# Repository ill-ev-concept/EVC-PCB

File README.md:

# EVC-PCB

*By: Himesh Nasaka*

Welcome to EV Concept's PCB Repo!

This is where all of our projects are stored. 

* Boards: Contains design files of all current boards being worked on
* Libs: Contains a wide selection of schematics, footprints, and models of components that are being used

# Getting Started

Start by having Git and KiCAD 10 downloaded. If you are using a older version of KiCAD, we recommend updating to the newest version. We also recommend installing Github Desktop in order to make the usage a bit cleaner.

Clone this repo. This can be either done through terminal or Github Desktop. Click the green dropdown labeled "<> Code" and select your preference of how to clone the repo. If using terminal, run the command below

```git clone [INSERT]```

If using Desktop, you can click the dropdown menu next to current repository, then "add", and finally "clone" where we can input the repo's url. 

# Setting Paths

After cloning, open KiCAD and find the "Preferences" dropdown and select "Configure Paths".
We are going to be adding three new paths. Create three new variables, ```EVC_SYMBOL_DIR```, ```EVC_FOOTPRINT_DIR```, and ```EVC_3DMODEL_DIR```. Link these to the location of the ```symbols```, ```footprints```, and ```3d_models``` folders contained with ```libs``` folder.

When designing, we will need KiCAD to know to look at a given library. We can do this by going to "Preferences" and finding either "Manage Symbol Libraries" or "Manage Footprint Libraries". Opening either brings up a window where we can select "Project Specific Libraries" where we can add paths. Click the folder icon and add the wanted library. If you set the path up correctly, the library path will contain  ```${EVC_SYMBOL_DIR}```, ```${EVC_FOOTPRINT_DIR}```, or ```${EVC_3DMODEL_DIR}```. 

# Contributing 

In order to begin designing, create a branch for your given board. This can be done through either the "current branch" dropdown in Desktop or using the command ```git checkout -b [branch name]```. You can swap branches using the same dropdown or either ```git checkout [branch name]```. 

This will be the branch where you will be doing your design work. Create a new KiCAD project and save the location into the boards folder of this repo. Everything onward will be traditional git. Use ```git add``` or check off the needed boxes on Desktop to add files for commit. ```git commit -m "[MESSAGE HERE]"``` will commit your changes. Make sure to write a meaningful commit message in order for good documentation. An example is shown below.

```git commit -m "Finished designing LDO and CANBus connectors, need to add MCU pinout and decoupling caps"```

Input both your contributions and the next required steps in order to give reminders to both yourself and your teammates. 

Once a board is finished or you want it reviewed, it must be submitted via a pull request. This can be done using ```git push -u origin [branch name]``` or by clicking the branch dropdown in Desktop and selecting the "create pull request" option.

This will open up a Github tab on your browser where you can edit your pull request. Give it a good title and description so the design choices are clear and understandable. A title will also help the leads parse what you guys want done. 

You'll see the image above if you use a command line prompt and go to the repo.

After the PR is submitted, we will decide on whether the board can be pushed to main or not. If it is not pushed, we will submit comments on what needs to be reviewed and edited. You can view open PRs and their comments in Github.

Apart from designing in KiCAD, it is important to be updating the libs folder when any new schematic, footprint, or model is added. First make sure the IC you want to add isn't currently within our library. Add the path to the specific library which is detailed more above. If the IC is not located in it's library, open Symbol/Footprint editor and select the library you want to add to. I recommended clicking the "View" dropdown, selecting the "Panels" option and adding the "Library Tree" option in order to easily see the connected libraries. 

From this, import the downloaded model and save the file. From there, push the updated library files and create a pull request. The leads will then check your work and merge it into main so everyone can use the IC.

When making pull requests for ICs, make sure to push them individually rather than with changes to other files. This will make it more clear for reviewers to understand that library files are being edited in addition to making sure that the change will be pushed to main. If you push with changes to your board and the pull request is not granted, people will not have access to the IC you have imported. 

Because the libs folder will be constantly updated, its also important to keep your branch up to date with new changes. We can layer on changes from main into our branch using a few different methods but the main one we will be using is merge. Run the command ```git fetch origin``` and then ```git merge origin``` in order to update changes. In Desktop, you can select "Update from main" from the "Branch" dropdown. 

This should not change any local files that is stored and will update the libs folder to have the newest selection of ICs. I recommend doing this every time you work on your boards. It will also make sure a merge conflict won't be created, in which the same file from two different pull requests is edited, causing a lot of hassle for the writers of this repo. 

A general outline of what the workflow may look like is shown below:

```git checkout [branch name]``` -> Run this to swap to the branch you want to work on

```git fetch origin``` -> Run this to pull updates from main. Important for having updated libs

```git merge origin/main``` -> Merges the changes from the above command

```git add [file name]``` -> Add files for commit. When updating library files, make sure to add them in individual PRs

```git commit -m "[message here]"``` -> Commits your changes to be pushed into your branch

```git push -u origin [branch name]``` -> Run this command the first time you make the branch. It will link your branch to Github. 

```git push``` -> Pushes your changes. After, you can go to Github and create a pull request for the changes to be pushed into main. **Don't create a PR for every change you do.** Only create pull requests **IF** you are editing the libs folder **OR** you are submitting for board revision **OR** it is the final revision of the board.

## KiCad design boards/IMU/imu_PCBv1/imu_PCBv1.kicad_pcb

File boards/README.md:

# Boards!

This is the location where you will be pushing your KiCAD files to. 
Each file should be it's own project. You should only be pushing 5 different files
- kicad_pro
- kicad_sch
- kicad_pcb
- fp-lib-table
- sym-lib-table

*Nothing else should be pushed*

I'll be adding more details later on

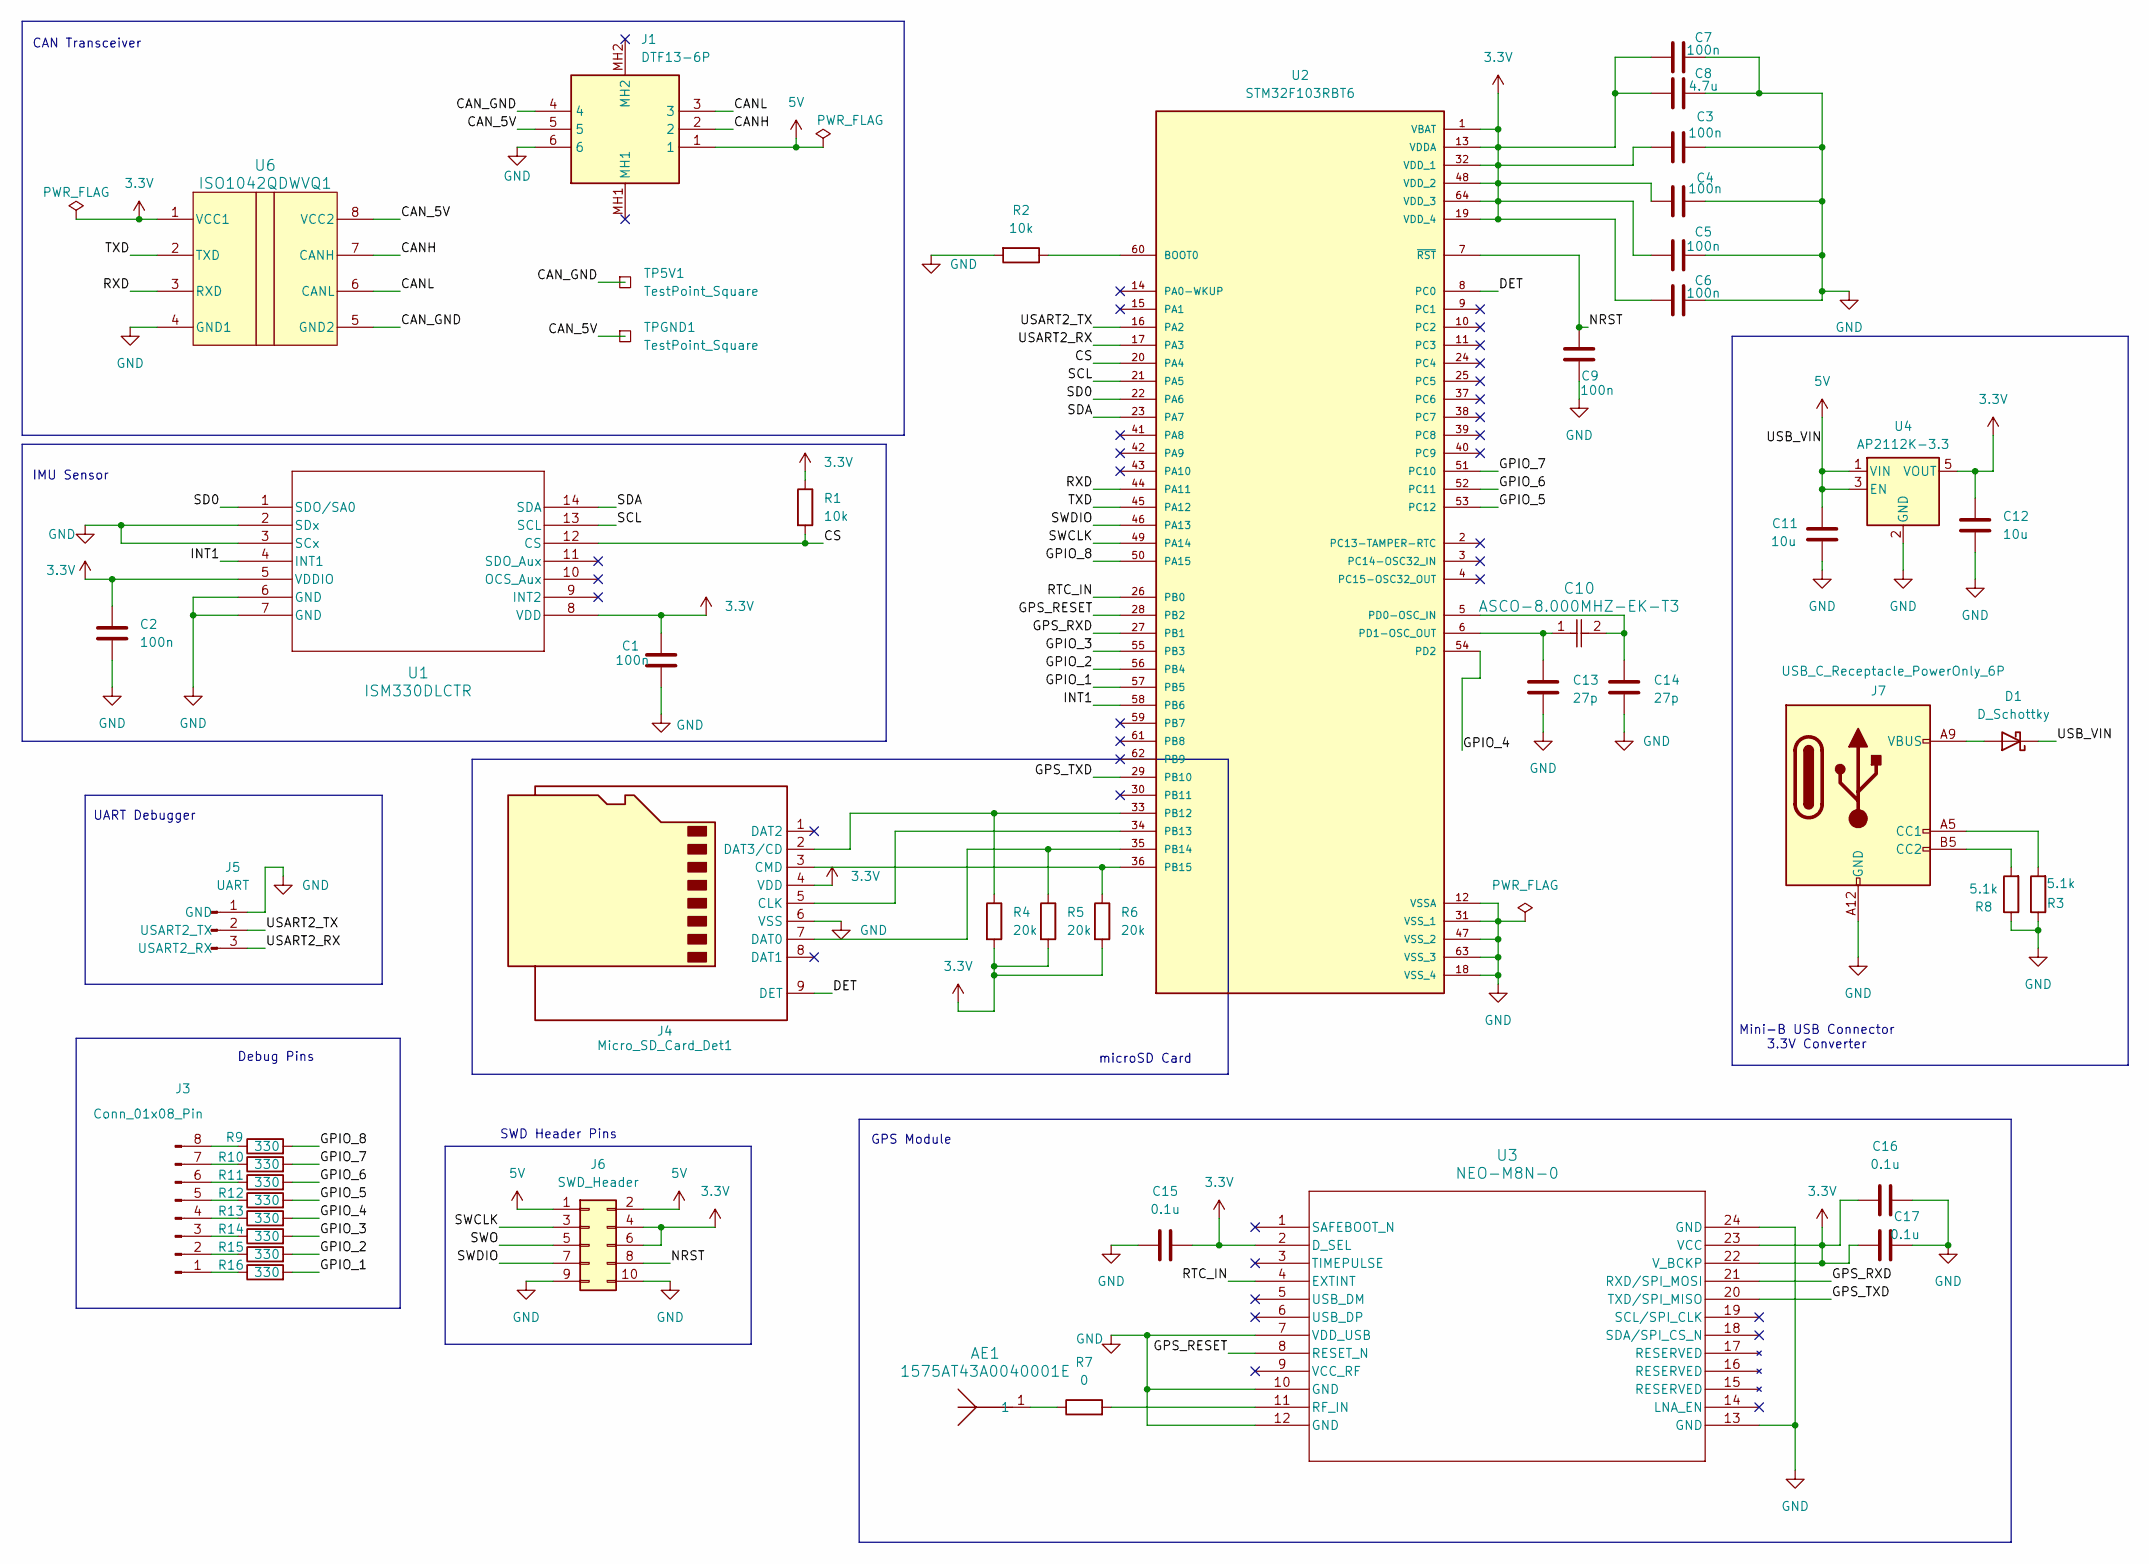
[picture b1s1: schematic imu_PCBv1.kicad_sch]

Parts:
AE1: 1575AT43A0040001E; antenna
C1, C2, C3, C4, C5, C6, C7, C9: 100n; C_0603_1608Metric_Pad1.08x0.95mm_HandSolder
C8: 4.7u; C_0603_1608Metric_Pad1.08x0.95mm_HandSolder
C10: ASCO-8.000MHZ-EK-T3; CAP_ASCO-8.000MHZ-EK-T3_ABR-M
C11, C12: 10u; C_0603_1608Metric_Pad1.08x0.95mm_HandSolder
C13, C14: 27p; C_0603_1608Metric_Pad1.08x0.95mm_HandSolder
C15, C16, C17: 0.1u; C_0603_1608Metric_Pad1.08x0.95mm_HandSolder
D1: D_Schottky; D_0603_1608Metric_Pad1.05x0.95mm_HandSolder
J1: DTF13-6P; EVC_CANconnector; Manufacturer_Part_Number DTF13-6P; Mouser Part Number 571-DTF13-6P
J3: Conn_01x08_Pin; PinHeader_1x08_P2.54mm_Vertical
J4: Micro_SD_Card_Det1; microSD_CardConnector_MSD-4-A
J5: UART; PinHeader_1x03_P2.54mm_Vertical
J6: SWD_Header; PinHeader_2x05_P2.54mm_Vertical
J7: USB_C_Receptacle_PowerOnly_6P; USB_Connector
R1, R2: 10k; R_0603_1608Metric_Pad0.98x0.95mm_HandSolder
R3, R8: 5.1k; R_0603_1608Metric_Pad0.98x0.95mm_HandSolder
R4, R5, R6: 20k; R_0603_1608Metric_Pad0.98x0.95mm_HandSolder
R7: 0; R_0603_1608Metric_Pad0.98x0.95mm_HandSolder
R9, R10, R11, R12, R13, R14, R15, R16: 330; R_0603_1608Metric_Pad0.98x0.95mm_HandSolder
TP5V1: TestPoint_Square; TestPoint_Pad_D2.0mm
TPGND1: TestPoint_Square; TestPoint_Pad_D2.0mm
U1: ISM330DLCTR; ISM330DLCTR-M
U2: STM32F103RBT6; STM32F103RBT6-10x10mm; PARTREV 20; DigiKey_Part_Number 497-6066-ND
U3: NEO-M8N-0; SNAP_NEO-M8N
U4: AP2112K-3.3; LinearRegulator_DIO-M
U6: ISO1042QDWVQ1; DWV0008A-IPC_A

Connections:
3.3V: C1.2, C2.2, C3.2, C4.2, C5.2, C6.2, C7.2, C8.2, C12.1, C15.1, C16.1, C17.1, J4.4 (VDD), J6.4, J6.6, R1.1, R4.2, R5.2, R6.2, U1.5 (VDDIO), U1.8 (VDD), U2.1 (VBAT), U2.13 (VDDA), U2.19 (VDD_4), U2.32 (VDD_1), U2.48 (VDD_2), U2.64 (VDD_3), U3.2 (D_SEL), U3.22 (V_BCKP), U3.23 (VCC), U4.5 (VOUT), U6.1 (VCC1)
5V: C11.2, D1.1 (K), J1.1, J6.1, J6.2, U4.1 (VIN), U4.3 (EN)
/CANH: J1.2, U6.7 (CANH)
/CANL: J1.3, U6.6 (CANL)
/CAN_5V: J1.5, TPGND1.1 (1_1), U6.8 (VCC2)
/CAN_GND: J1.4, TP5V1.1 (1_1), U6.5 (GND2)
/CS: R1.2, U1.12 (CS), U2.20 (PA4)
/DET: J4.9 (DET), U2.8 (PC0)
/GPIO_1: R16.2, U2.57 (PB5)
/GPIO_2: R15.2, U2.56 (PB4)
/GPIO_3: R14.2, U2.55 (PB3)
/GPIO_4: R13.2, U2.54 (PD2)
/GPIO_5: R12.2, U2.53 (PC12)
/GPIO_6: R11.2, U2.52 (PC11)
/GPIO_7: R10.2, U2.51 (PC10)
/GPIO_8: R9.2, U2.50 (PA15)
/GPS_RESET: U2.28 (PB2), U3.8 (RESET_N)
/GPS_RXD: U2.27 (PB1), U3.21 (RXD/SPI_MOSI)
/GPS_TXD: U2.29 (PB10), U3.20 (TXD/SPI_MISO)
/INT1: U1.4 (INT1), U2.58 (PB6)
/NRST: C9.2, J6.8, U2.7 (~RST)
/RTC_IN: U2.26 (PB0), U3.4 (EXTINT)
/RXD: U2.44 (PA11), U6.3 (RXD)
/SCL: U1.13 (SCL), U2.21 (PA5)
/SD0: U1.1 (SDO/SA0), U2.22 (PA6)
/SDA: U1.14 (SDA), U2.23 (PA7)
/SWCLK: J6.3, U2.49 (PA14)
/SWDIO: J6.7, U2.46 (PA13)
/SWO: J6.5
/TXD: U2.45 (PA12), U6.2 (TXD)
/USART2_RX: J5.3 (USART2_RX), U2.17 (PA3)
/USART2_TX: J5.2 (USART2_TX), U2.16 (PA2)
GND: C1.1, C2.1, C3.1, C4.1, C5.1, C6.1, C7.1, C8.1, C9.1, C11.1, C12.2, C13.2, C14.2, C15.2, C16.2, C17.2, J1.6, J4.6 (VSS), J5.1 (GND), J6.9, J6.10, J7.A12 (GND), J7.B12 (GND), R2.2, R3.1, R8.1, U1.2 (SDx), U1.3 (SCx), U1.6 (GND), U1.7 (GND), U2.12 (VSSA), U2.18 (VSS_4), U2.31 (VSS_1), U2.47 (VSS_2), U2.63 (VSS_3), U3.7 (VDD_USB), U3.10 (GND), U3.12 (GND), U3.13 (GND), U3.24 (GND), U4.2 (GND), U6.4 (GND1); also elsewhere on the board
unnamed: AE1.1 (1_1), R7.1
unnamed: D1.2 (A), J7.A9 (VBUS), J7.B9 (VBUS)
unnamed: J3.1, R16.1
unnamed: J3.2, R15.1
unnamed: J3.3, R14.1
unnamed: J3.4, R13.1
unnamed: J3.5, R12.1
unnamed: J3.6, R11.1
unnamed: J3.7, R10.1
unnamed: J3.8, R9.1
unnamed: J4.5 (CLK), U2.34 (PB13)
unnamed: J4.3 (CMD), R6.1, U2.36 (PB15)
unnamed: J4.7 (DAT0), R5.1, U2.35 (PB14)
unnamed: J4.2 (DAT3/CD), R4.1, U2.33 (PB12)
unnamed: J7.A5 (CC1), R3.2
unnamed: J7.B5 (CC2), R8.2
unnamed: R2.1, U2.60 (BOOT0)
unnamed: R7.2, U3.11 (RF_IN)

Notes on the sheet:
microSD Card
GPS Module
Mini-B USB Connector 3.3V Converter
UART Debugger
Debug Pins
SWD Header Pins
IMU Sensor
CAN Transceiver

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
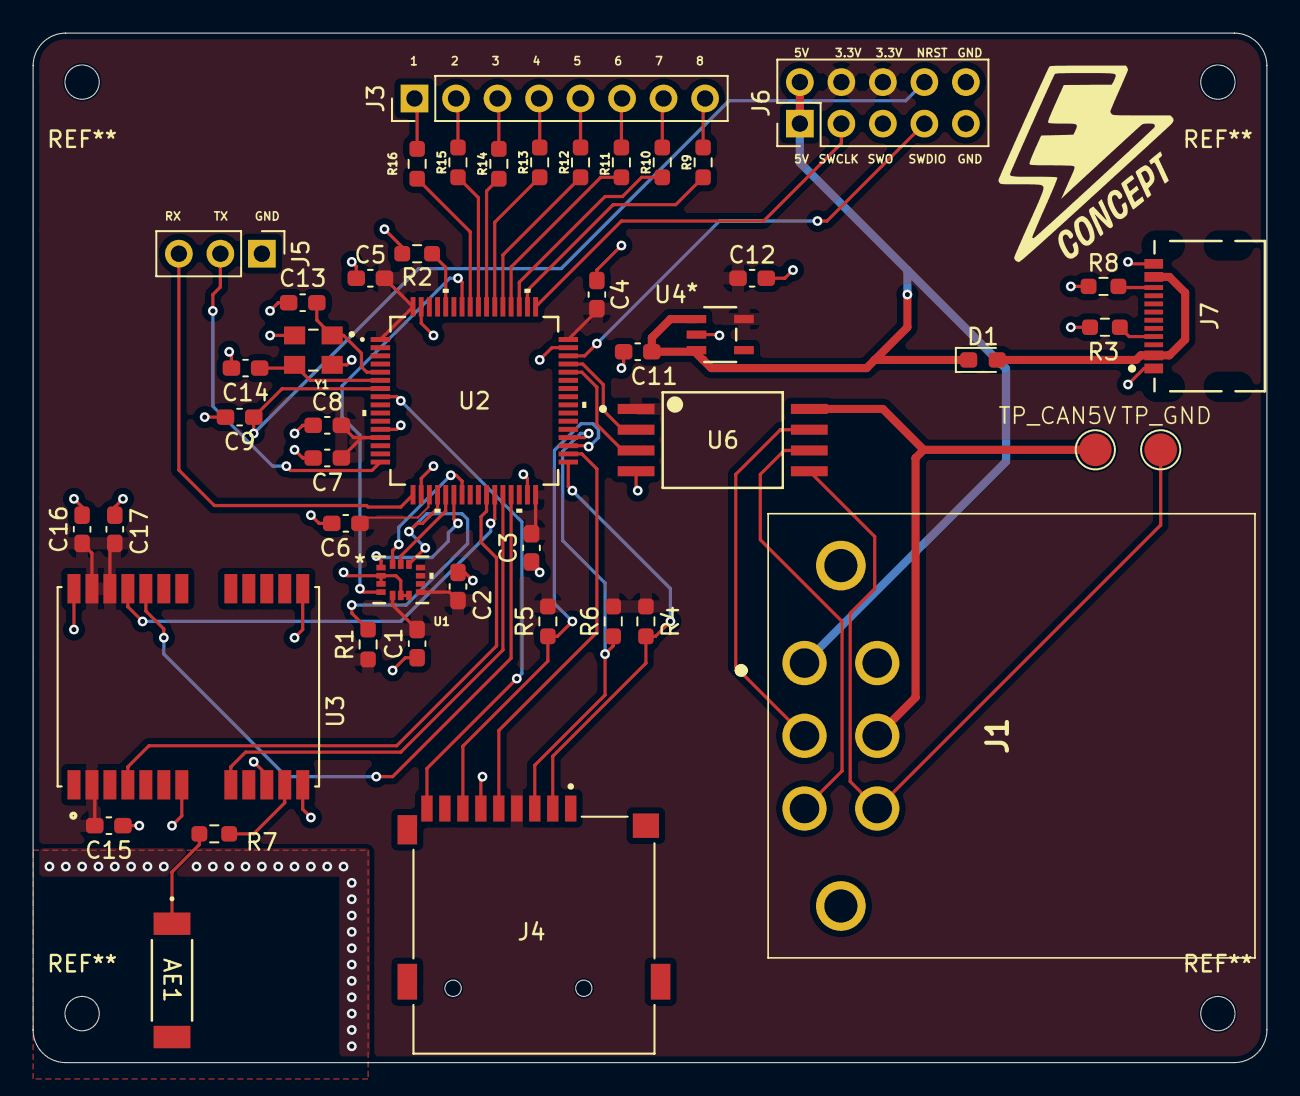
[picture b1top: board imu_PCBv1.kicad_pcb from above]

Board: 2 copper layers, 75.5 x 63.0 mm, 48 parts (0 on the bottom side), 52 nets.

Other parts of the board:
Y1: ECS-80-12-33-JGN-TR; XTAL_ECS-240-8-33-AGN-TR

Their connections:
GND: Y1.2 (GND), Y1.4 (GND__1); also elsewhere on the board

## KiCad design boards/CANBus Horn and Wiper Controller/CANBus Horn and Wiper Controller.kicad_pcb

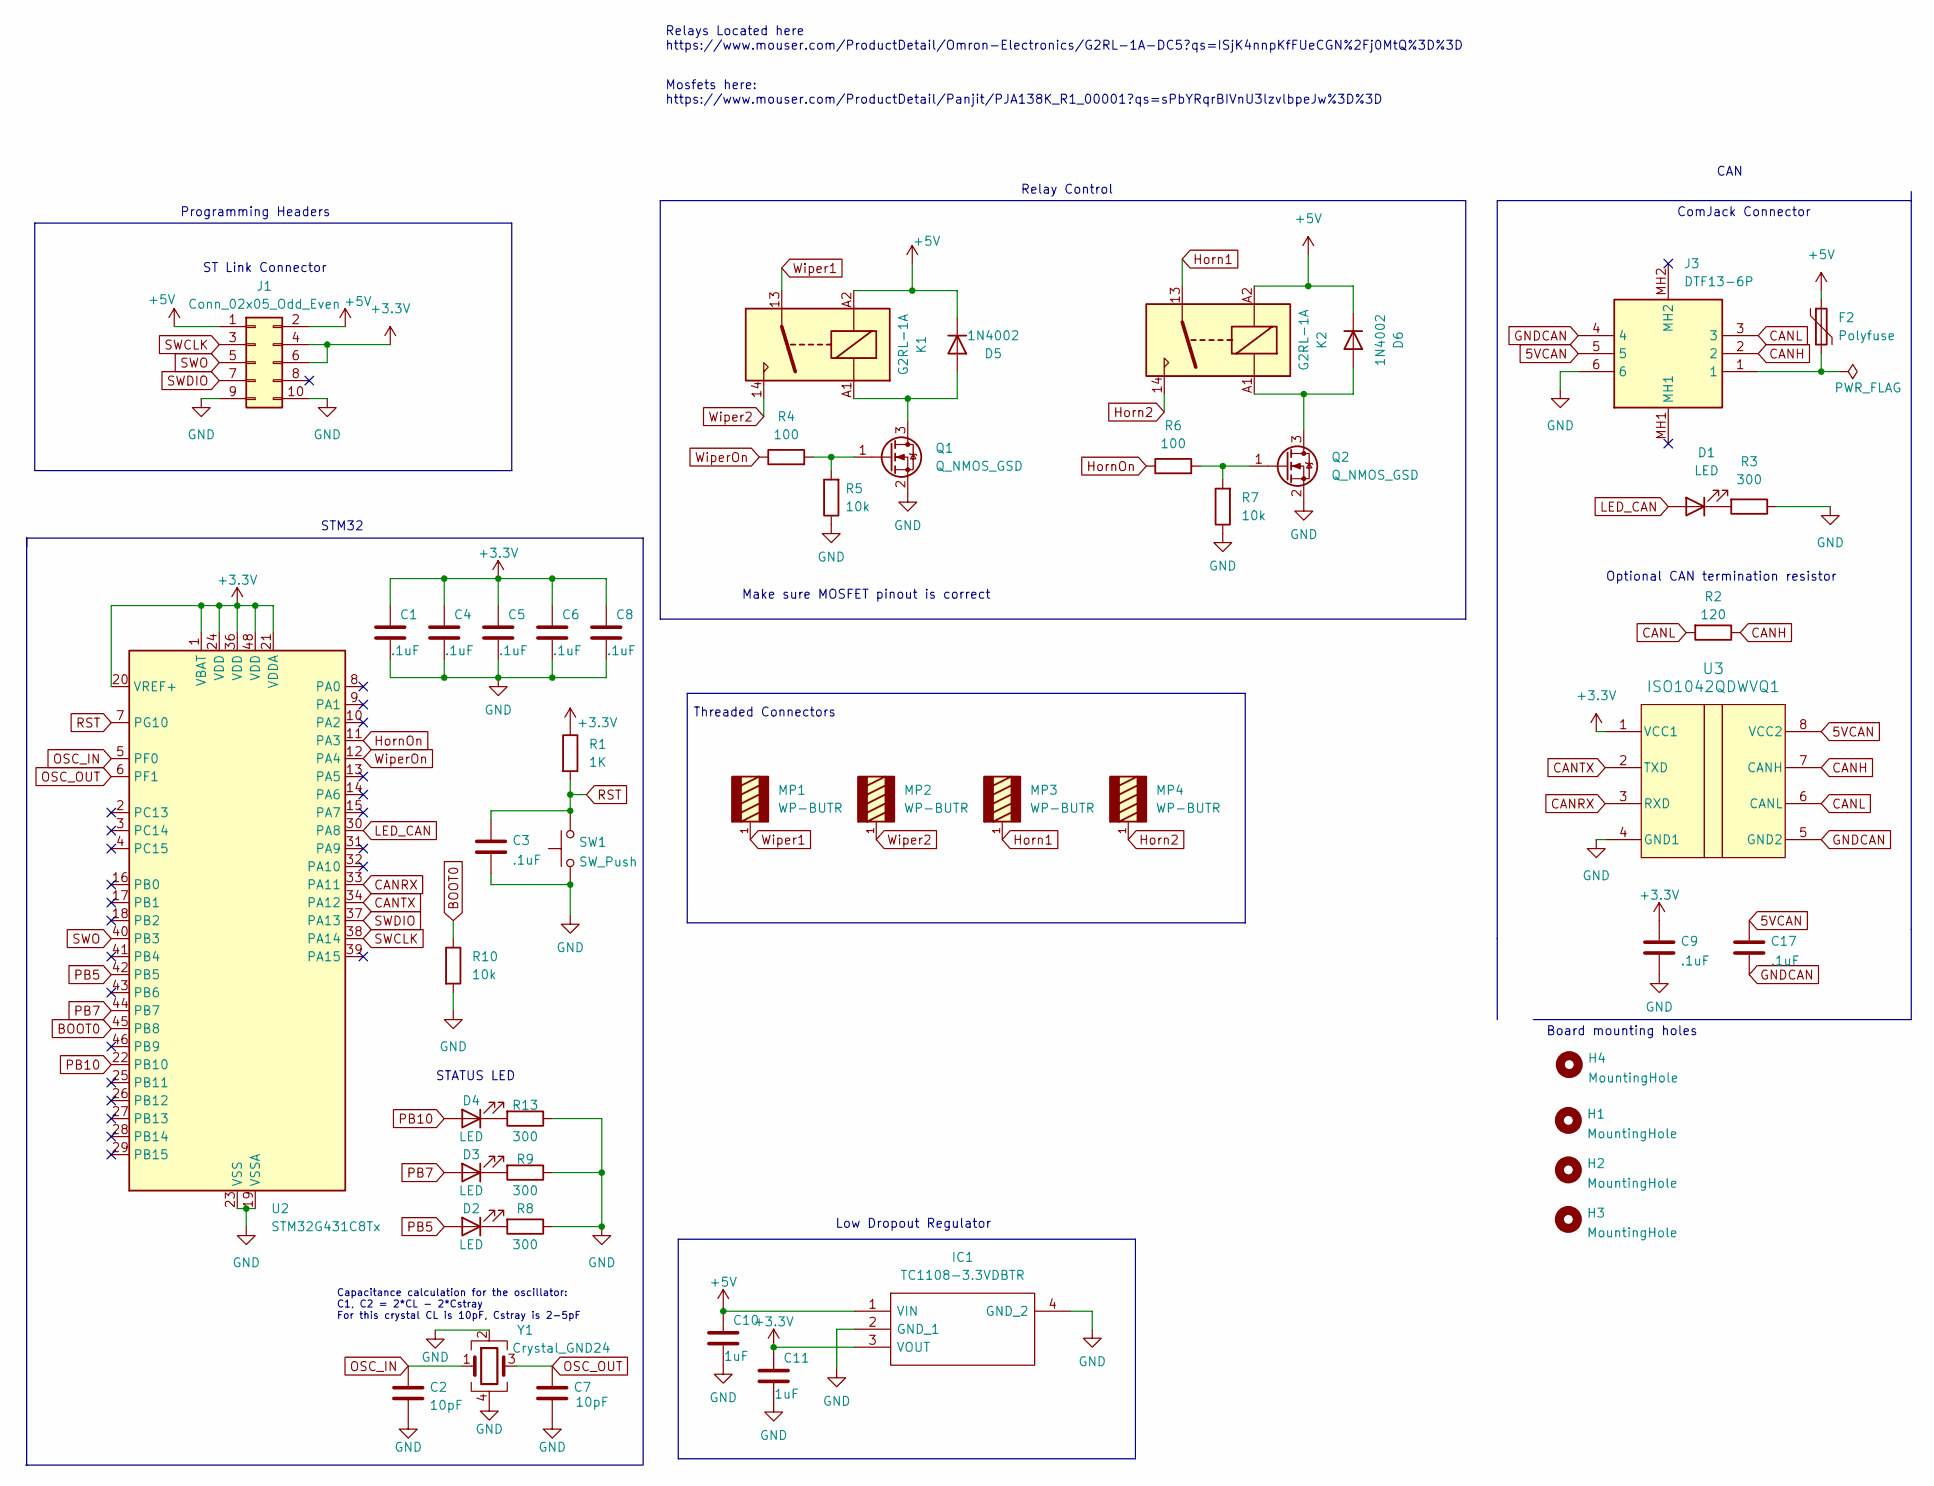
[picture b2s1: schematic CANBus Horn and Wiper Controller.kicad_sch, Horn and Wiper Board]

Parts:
C1, C3, C4, C5, C6, C8, C9, C17: .1uF; C_0805_2012Metric
C2, C7: 10pF; C_0603_1608Metric
C10, C11: 1uF; C_0805_2012Metric
D1, D2, D3, D4: LED; LED_0603_1608Metric
D5, D6: 1N4002; D_DO-41_SOD81_P10.16mm_Horizontal
F2: Polyfuse; Fuse_0805_2012Metric
H1, H2, H3, H4: MountingHole; MountingHole_3.2mm_M3
IC1: TC1108-3.3VDBTR; SOT230P700X180-4N; Mouser Part Number 579-TC1108-3.3VDBTR
J1: Conn_02x05_Odd_Even; PinSocket_2x05_P2.54mm_Vertical
J3: DTF13-6P; DTF136P; Manufacturer_Part_Number DTF13-6P; Mouser Part Number 571-DTF13-6P
K1, K2: G2RL-1A; Relay_SPST_Omron_G2RL-1A
MP1, MP2, MP3, MP4: WP-BUTR; WP-BUTR_7460307; DigiKey_Part_Number 732-3201-ND
Q1, Q2: Q_NMOS_GSD; SOT-23-3
R1: 1K; R_0805_2012Metric
R2: 120; R_0805_2012Metric
R3, R8, R9, R13: 300; R_0805_2012Metric
R4, R6: 100; R_0805_2012Metric
R5, R7, R10: 10k; R_0805_2012Metric
SW1: SW_Push; SW_Push_SPST_NO_Alps_SKRK
U2: STM32G431C8Tx; LQFP-48_7x7mm_P0.5mm
U3: ISO1042QDWVQ1; SOIC8_ISO1042-Q1
Y1: Crystal_GND24; Crystal_SMD_3225-4Pin_3.2x2.5mm

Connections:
5VCAN: C17.1, J3.5, U3.8 (VCC2)
+3.3V: C1.1, C4.1, C5.1, C6.1, C8.1, C9.1, C11.1, IC1.3 (VOUT), J1.4, J1.6, R1.1, U2.1 (VBAT), U2.20 (VREF+), U2.21 (VDDA), U2.24 (VDD), U2.36 (VDD), U2.48 (VDD), U3.1 (VCC1)
+5V: C10.1, D5.1 (K), D6.1 (K), F2.1, IC1.1 (VIN), J1.1, J1.2, K1.A2, K2.A2
BOOT0: R10.1, U2.45 (PB8)
CANH: J3.2, R2.1, U3.7 (CANH)
CANL: J3.3, R2.2, U3.6 (CANL)
CANRX: U2.33 (PA11), U3.3 (RXD)
CANTX: U2.34 (PA12), U3.2 (TXD)
GND: C1.2, C2.2, C3.2, C4.2, C5.2, C6.2, C7.2, C8.2, C9.2, C10.2, C11.2, IC1.2 (GND_1), IC1.4 (GND_2), J1.9, J1.10, J3.6, Q1.2 (S), Q2.2 (S), R3.1, R5.1, R7.1, R8.1, R9.1, R10.2, R13.1, SW1.1, U2.19 (VSSA), U2.23 (VSS), U2.35 (VSS), U2.47 (VSS), U3.4 (GND1), Y1.2, Y1.4
GNDCAN: C17.2, J3.4, U3.5 (GND2)
Horn1: K2.13, MP3.1, MP3.2, MP3.3, MP3.4, MP3.5, MP3.6, MP3.7, MP3.8
Horn2: K2.14, MP4.1, MP4.2, MP4.3, MP4.4, MP4.5, MP4.6, MP4.7, MP4.8
HornOn: R6.1, U2.11 (PA3)
LED_CAN: D1.2 (A), U2.30 (PA8)
unnamed: D1.1 (K), R3.2
unnamed: D2.1 (K), R8.2
unnamed: D3.1 (K), R9.2
unnamed: D4.1 (K), R13.2
unnamed: D5.2 (A), K1.A1, Q1.3 (D)
unnamed: D6.2 (A), K2.A1, Q2.3 (D)
unnamed: F2.2, J3.1
unnamed: Q1.1 (G), R4.2, R5.2
unnamed: Q2.1 (G), R6.2, R7.2
OSC_IN: C2.1, U2.5 (PF0), Y1.1
OSC_OUT: C7.1, U2.6 (PF1), Y1.3
PB5: D2.2 (A), U2.42 (PB5)
PB7: D3.2 (A), U2.44 (PB7)
PB10: D4.2 (A), U2.22 (PB10)
RST: C3.1, R1.2, SW1.2, U2.7 (PG10)
SWCLK: J1.3, U2.38 (PA14)
SWDIO: J1.7, U2.37 (PA13)
SWO: J1.5, U2.40 (PB3)
Wiper1: K1.13, MP1.1, MP1.2, MP1.3, MP1.4, MP1.5, MP1.6, MP1.7, MP1.8
Wiper2: K1.14, MP2.1, MP2.2, MP2.3, MP2.4, MP2.5, MP2.6, MP2.7, MP2.8
WiperOn: R4.1, U2.12 (PA4)

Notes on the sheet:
Threaded Connectors
Optional CAN termination resistor
Relays Located here https://www.mouser.com/ProductDetail/Omron-Electronics/G2RL-1A-DC5?qs=ISjK4nnpKfFUeCGN%2Fj0MtQ%3D%3D
CAN
Mosfets here: https://www.mouser.com/ProductDetail/Panjit/PJA138K_R1_00001?qs=sPbYRqrBIVnU3lzvlbpeJw%3D%3D
Make sure MOSFET pinout is correct
ST Link Connector
Programming Headers
STM32
Capacitance calculation for the oscillator: C1, C2 = 2*CL - 2*Cstray For this crystal CL is 10pF, Cstray is 2-5pF
Low Dropout Regulator
STATUS LED
Board mounting holes
Relay Control
ComJack Connector

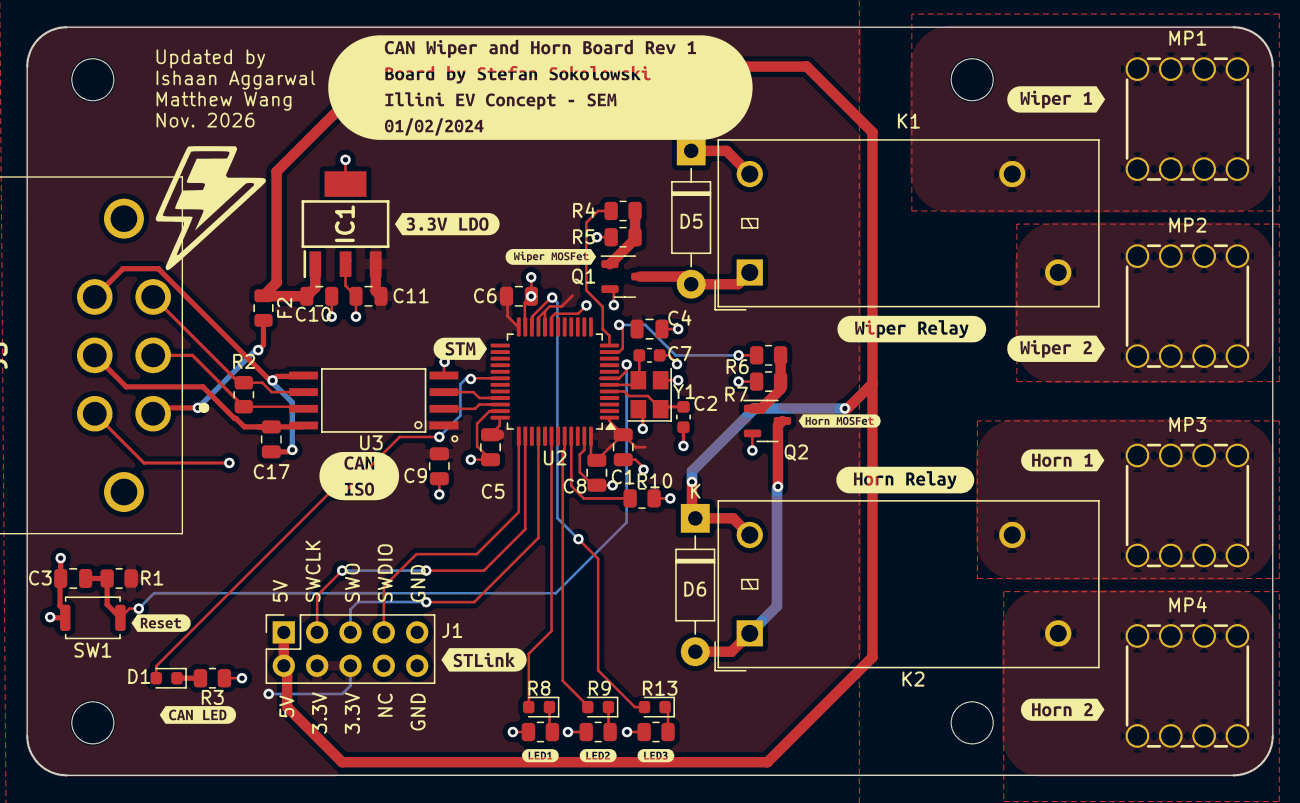
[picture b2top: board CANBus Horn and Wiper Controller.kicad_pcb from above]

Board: 2 copper layers, 94.9 x 57.0 mm, 67 parts (0 on the bottom side), 35 nets.

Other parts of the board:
kibuzzard-6594C8CC: G***; kibuzzard-6594C8CC
kibuzzard-6594C8F6: G***; kibuzzard-6594C8F6
kibuzzard-6594C90C: G***; kibuzzard-6594C90C
kibuzzard-6594C936: G***; kibuzzard-6594C936
kibuzzard-6594D3A6: G***; kibuzzard-6594D3A6
kibuzzard-6594D3A9: G***; kibuzzard-6594D3A9
kibuzzard-6594D34E: G***; kibuzzard-6594D34E
kibuzzard-6594D39D: G***; kibuzzard-6594D39D
kibuzzard-6594ECBA: G***; kibuzzard-6594ECBA
kibuzzard-6594ECC0: G***; kibuzzard-6594ECC0
kibuzzard-6594ECC9: G***; kibuzzard-6594ECC9
kibuzzard-6594ECCC: G***; kibuzzard-6594ECCC
kibuzzard-6594ED5E: G***; kibuzzard-6594ED5E
kibuzzard-6594ED81: G***; kibuzzard-6594ED81
kibuzzard-6594EE0A: G***; kibuzzard-6594EE0A
kibuzzard-6594EE20: G***; kibuzzard-6594EE20
kibuzzard-6594EF8F: G***; kibuzzard-6594EF8F
kibuzzard-6593999E: G***; kibuzzard-6593999E

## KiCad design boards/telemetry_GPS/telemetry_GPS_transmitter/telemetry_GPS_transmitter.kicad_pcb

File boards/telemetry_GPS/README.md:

## Cart Orders

Mouser Cart(enough for 2 board, with some tolerance in the number of passives): https://www.mouser.com/en/Tools/SavedCart/Share?AccessID=8379b7a41d

Digikey Cart(enough for 2 boards with some tolerance in the number of passives): https://www.digikey.com/short/d59q1043

## Block Diagram

## Common Issues/Tips

- The recommended way to solder this board is to use a stencil for the top side, place all components (except for buttons & connectors) on the solder paste, and use a reflow oven. For the back side, it's recommended to use the backside stencil as well as a heat gun. Try to be careful with applying heat around the UBLOX NEO-M8N area. DO NOT UNDER ANY CIRCUMSTANCES SOLDER THE BACK SIDE IN AN OVEN AFTER REFLOWING THE TOP SIDE.
- Always use a microscope when debugging your soldering of the telemetry "Scout" board
- Stencil
  - Make sure that the stencil is relatively flat onto the board, otherwise you'll do multiple tries and end up with way too much paste
  - Pins shouldn't have a ton of solder but always make sure to check that EVERY pin has solder
- MCU Orientation
  - The dot on the bottom left of the MCU marks pin 1, don't be fooled by anything else. If you did it correctly, the ST logo should be on the bottom left while looking at the board top-down, and the U1 label on the left side of the MCU
- BGA
  - The BALFHB uses BGA pins. These pins already come pre-tinned so do not apply solder on those pads, simply place the component down onto the pads.
  - If you suspect that the component is not flush/a couple pins are unconnected, apply flux and use the heat gun, flux is your best friend

## Instructions for a future V2 board
- Look into storing the data onto an SD card
- Add an LED to the GPS chip's PPS to verify that it is on
- Add more test points in general
- Do research into expanding the BALFHB into actual inductors and capacitors to make soldering the board less annoying
- Add a sort of "Faraday Cage" around the MCU, crystal, and RF matching network, kind of like the one on the NUCLEO-WL55JC1 (pictured below)

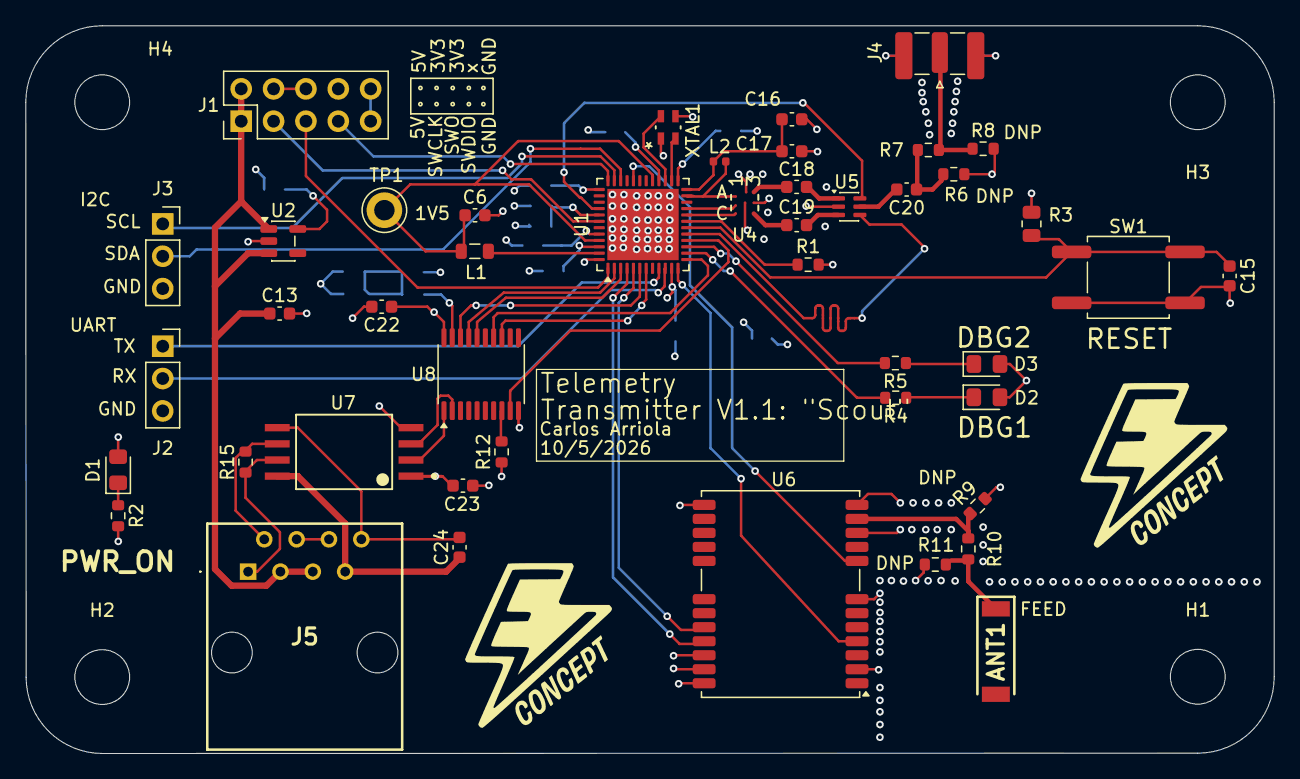
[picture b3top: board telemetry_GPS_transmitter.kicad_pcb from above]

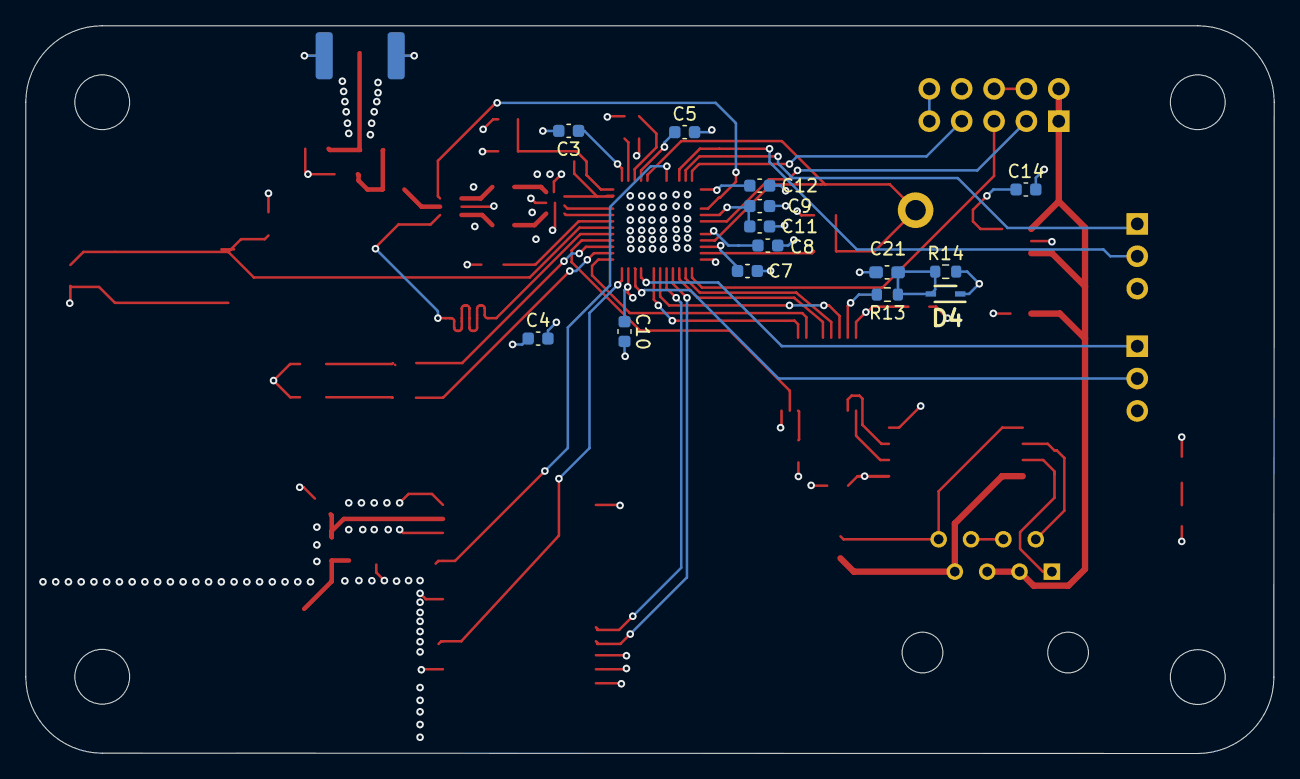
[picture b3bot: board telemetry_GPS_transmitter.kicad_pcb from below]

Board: 4 copper layers, 98.0 x 57.1 mm, 65 parts (14 on the bottom side), 55 nets.

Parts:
ANT1: 1575AT43A0040001E; ANTC7020X90N
C3, C5, C7, C8, C10, C15, C22, C23, C24: 0.1uF; C_0603_1608Metric
C4, C11, C12: 4.7uF; C_0603_1608Metric
C6: 470nF; C_0603_1608Metric
C9: 0.01uF; C_0603_1608Metric
C13, C14: 1uF; C_0603_1608Metric
C16: 47nF; C_0603_1608Metric
C17: 68pF; C_0603_1608Metric
C18, C19, C20: 1000pF; C_0603_1608Metric
C21: 2.2nF; C_0603_1608Metric_Pad1.08x0.95mm_HandSolder
D1, D2, D3: LED_Green; LED_0805_2012Metric_Pad1.15x1.40mm_HandSolder
D4: 1N4148WS; SODFL2512X90N
G1, G1#2: LOGO; EVC_LOGO
H1, H2, H3, H4: MountingHole; MountingHole_4.3mm_M4
J1: Conn_02x05_Odd_Even; PinHeader_2x05_P2.54mm_Vertical
J2, J3: Conn_01x03; PinSocket_1x03_P2.54mm_Vertical
J4: Conn_Coaxial; SMA_Samtec_SMA-J-P-H-ST-EM1_EdgeMount
J5: 54602-908LF; 54602908LF
L1: 15uH; L_0805_2012Metric
L2: 47nH (High Q); L_0402_1005Metric
R1: 10K; R_0603_1608Metric
R2, R4, R5: 330R; R_0603_1608Metric
R3: 100k; R_0805_2012Metric
R6, R8, R9, R11: R; R_0603_1608Metric
R7, R10: 0R; R_0603_1608Metric
R12, R13: 10k; R_0603_1608Metric
R14: 1k; R_0603_1608Metric
R15: 120R; R_0603_1608Metric
SW1: SW_Push; SW_Push_1P1T_NO_CK_KSC9xxG
TP1: TestPoint; TestPoint_Keystone_5010-5014_Multipurpose
U1: STM32WL55CCUx; QFN-48-1EP_7x7mm_P0.5mm_EP5.6x5.6mm
U2: TLV75533PDBV; SOT-23-5
U4: BALFHB-WL-02D3; CSPG8_STM
U5: MASW-007221; SOT-363_SC-70-6
U6: NEO-M8N; ublox_NEO
U7: ISO1042QDWVQ1; DWV0008A-IPC_B
U8: MCP2515-xST; TSSOP-20_4.4x6.5mm_P0.65mm
XTAL1: NX2016SA-32MHZ-EXS00A-CS07977; NX2016SA_NDK

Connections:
+1V5: C6.1, L1.1, TP1.1 (1_1), U1.29 (VDDRF1V55), U1.45 (VFBSMPS)
+3V3: C3.1, C4.1, C5.1, C7.1, C8.1, C9.1, C10.1, C11.1, C12.1, C14.1, C22.1, C23.1, D1.2 (A), D2.2 (A), D3.2 (A), D4.1 (K), J1.4, J1.6, R3.1, R14.2, U1.11 (VDD), U1.25 (VDDPA), U1.28 (VDDRF), U1.37 (VBAT), U1.41 (VDDA), U1.44 (VDD), U1.46 (VDDSMPS), U2.5 (OUT), U6.2 (D_SEL), U6.22 (V_BCKP), U6.23 (VCC), U7.1 (VCC1), U8.20 (VDD)
+5V: C13.1, J1.1, J1.2, J5.3, J5.5, U2.1 (IN), U2.3 (EN)
/CAN/5VCAN: C24.1, J5.7, U7.8 (VCC2)
/CAN/CANH: J5.1, R15.1, U7.7 (CANH)
/CAN/CANL: J5.2, R15.2, U7.6 (CANL)
/CAN/CAN_RX: U7.3 (RXD), U8.2 (RXCAN)
/CAN/CAN_TX: U7.2 (TXD), U8.1 (TXCAN)
/CAN/CS_N: U1.6 (PB8), U8.18 (~CS)
/CAN/EXT_CLK: U1.16 (PA8), U8.9 (OSC1)
/CAN/GNDCAN: C24.2, J5.8, U7.5 (GND2)
/CAN/INT_N: U1.7 (PA0), U8.13 (~INT)
/CAN/SCLK: U1.13 (PA5), U8.14 (SCK)
/CAN/SLAVE_I: U1.3 (PB5), U8.16 (SI)
/CAN/SLAVE_O: U1.2 (PB4), U8.17 (SO)
/Debug/DBG_LED_1: R4.2, U1.14 (PA6)
/Debug/DBG_LED_2: R5.2, U1.15 (PA7)
/Debug/I2C_SCL: J3.1, U1.35 (PA12)
/Debug/I2C_SDA: J3.2, U1.34 (PA11)
/Debug/MCU_UART_RX: J2.2, U1.10 (PA3)
/Debug/MCU_UART_TX: J2.1, U1.9 (PA2)
/Debug/NRST: C15.1, R3.2, SW1.1, U1.18 (NRST)
/Debug/SWCLK: J1.3, U1.42 (PA14)
/Debug/SWDIO: J1.7, U1.36 (PA13)
/Debug/SWO: J1.5, U1.1 (PB3)
/GPS/RESET_N: U1.32 (PB12), U6.8 (~RESET)
/GPS/RTC_IN: U1.12 (PA4), U6.4 (EXTINT)
/GPS/RXD: U1.4 (PB6), U6.21 (RXD/SPI_MOSI)
/GPS/TXD: U1.5 (PB7), U6.20 (TXD/SPI_MISO)
/RF/RFI_N: U1.21 (RFI_N), U4.A2 (RFI_N_OUT)
/RF/RFI_P: U1.20 (RFI_P), U4.A3 (RFI_P_OUT)
/RF/RFO_HP: L2.2, U1.23 (RFO_HP), U4.A1 (RFO_IN)
/RF/RF_I: C19.1, U4.C3 (RFI_IN)
/RF/RF_O: C18.2, U4.C1 (RFO_OUT)
/RF/RF_TX_EN: U1.40 (PC15), U5.6 (V1)
/RF/RF_TX_EN_N: U1.17 (PA9), U5.4 (V2)
/RF/VR_PA: C16.1, C17.1, L2.1, U1.24 (VR_PA)
/STM32/OSC_IN: U1.26 (OSC_IN), XTAL1.1
/STM32/OSC_OUT: U1.27 (OSC_OUT), XTAL1.3
GND: C3.2, C4.2, C5.2, C6.2, C7.2, C8.2, C9.2, C10.2, C11.2, C12.2, C13.2, C14.2, C15.2, C16.2, C17.2, C21.2, C22.2, C23.2, J1.9, J1.10, J2.3, J3.3, J4.2 (Ext), J5.4, J5.6, R1.2, R2.2, R6.2, R8.2, R9.2, R11.2, R12.1, SW1.2, U1.48 (VSSSMPS), U1.49 (VSS), U2.2 (GND), U4.B1 (GND2), U4.B2 (GND3), U4.C2 (GND1), U5.2 (GND), U6.7 (VDD_USB), U6.10 (GND), U6.12 (GND), U6.13 (GND), U6.24 (GND), U7.4 (GND1), U8.10 (VSS), XTAL1.2, XTAL1.4
unnamed: ANT1.1 (FEED_1), R10.2, R11.1
unnamed: C20.1, R6.1, R7.1
unnamed: D1.1 (K), R2.1
unnamed: D2.1 (K), R4.1
unnamed: D3.1 (K), R5.1
unnamed: C21.1, D4.2 (A), R13.1, R14.1
unnamed: J4.1 (In), R7.2, R8.1
unnamed: R1.1, U1.19 (PH3)
unnamed: L1.2, U1.47 (VLXSMPS)
unnamed: C18.1, U5.1 (RF1)
unnamed: C19.2, U5.3 (RF2)
unnamed: C20.2, U5.5 (RFC)
unnamed: R9.1, R10.1, U6.11 (RF_IN)
unnamed: R12.2, U8.8 (OSC2)
unnamed: R13.2, U8.19 (~RESET)
